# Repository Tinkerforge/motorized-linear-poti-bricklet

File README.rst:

Motorized Linear Poti Bricklet
==============================

This repository contains the firmware source code and the hardware design
files. The documentation generator configs can be found at
https://github.com/Tinkerforge/generators

Repository Content
------------------

software/:
 * examples/: Examples for all supported languages
 * build/: Compiled files
 * src/: Source code of firmware
 * Makefile: Makefile to build project

hardware/:
 * Contains KiCad project files and additionally schematics as PDF

datasheets/:
 * Contains datasheets for sensors and complex ICs that are used

Hardware
--------

The hardware is designed with the open source EDA Suite KiCad
(http://www.kicad.org). Before you are able to open the files,
you have to install the Tinkerforge kicad-libraries
(https://github.com/Tinkerforge/kicad-libraries). You can either clone
them directly in hardware/ or clone them in a separate folder and
symlink them into hardware/
(ln -s kicad_path/kicad-libraries project_path/hardware). After that you
can open the .pro file in hardware/ with KiCad and from there view and
modify the schematics and the PCB layout.

Software
--------

If you want to do your own Brick/Bricklet firmware development we highly
recommend that you use our build environment setup script and read the
tutorial (https://www.tinkerforge.com/en/doc/Tutorials/Tutorial_Build_Environment/Tutorial.html).

To compile the C code we recommend you to install the newest GNU Arm Embedded
Toolchain (https://launchpad.net/gcc-arm-embedded/+download).
You also need to install bricklib2 (https://github.com/Tinkerforge/bricklib2).

You can either clone it directly in software/src/ or clone it in a
separate folder and symlink it into software/src/
(ln -s bricklib_path/bricklib2 project_path/software/src/). Finally make sure to
have CMake installed (http://www.cmake.org/cmake/resources/software.html).

After that you can build the firmware by invoking make in software/.
The firmware (.zbin) can then be found in software/build/ and uploaded
with brickv (click button "Flashing" on start screen).

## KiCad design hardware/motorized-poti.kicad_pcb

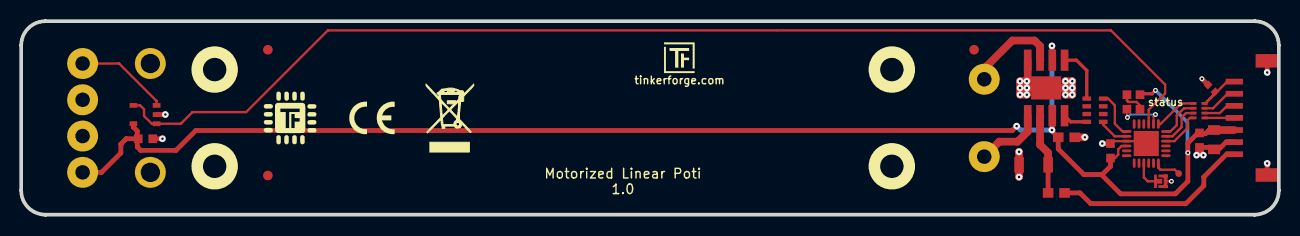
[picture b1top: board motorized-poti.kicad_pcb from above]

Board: 2 copper layers, 130.0 x 20.0 mm, 27 parts (0 on the bottom side), 24 nets.

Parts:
C1: 100nF; C0603E
C2: 10µF; C0805
C3: 47uF/10V; C1206
C4, C101: 100nF; C0603F
C5: 1µF; C0603F
C6: 220pF; C0402F
D1: blue; D0603F
Fiducial_Mark: VAL**; Fiducial_Mark
Fiducial_Mark#2, Fiducial_Mark#3: VAL**; Fiducial_Mark
J101: Debug; DEBUG_PAD
L1: FB; C0603E
P1: CON-SENSOR2
P2: MOTORIZED_POTI
P3: BOOT; SolderJumper
R1: 1k; R0603F
RP1: 1k; 4X0603
RP3: 82; 4X0402
U1: XMC1100-16; QFN24-4x4mm-0.5mm
U2: ZXBM5210; SO-8-EP
U3, U4, U5, U6: DRILL; DRILL_NP
U101: TLV271IDBVR; SOT23-5
VAL: CE_5mm

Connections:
+5V: L1.1, P1.1
AIN: U1.3, U101.1, U101.4
FWD: RP1.8, U1.8
GND: C1.2, C2.2, C3.1, C4.2, C5.2, C6.2, C101.2, P1.2, P1.EP, P2.3, P3.1, U1.9, U1.EXP, U2.8, U2.EP, U101.2
unnamed: C3.2, L1.2, U2.2
unnamed: C6.1, P1.7, RP3.4
unnamed: D1.2, R1.1
unnamed: J101.1, U1.18
unnamed: P1.4, RP3.1
unnamed: P1.5, RP3.2
unnamed: P1.6, RP3.3
unnamed: P2.4, U101.3
unnamed: P2.A, U2.7
unnamed: P2.B, U2.1
unnamed: P3.2, U1.15
unnamed: R1.2, U1.2
unnamed: RP1.1, U2.4
unnamed: RP1.4, U2.5
REV: RP1.5, U1.7
S-CLK: RP3.7, U1.23
S-CS: RP3.8, U1.22
S-MISO: RP3.5, U1.1
S-MOSI: RP3.6, U1.24
VCC: C1.1, C2.1, C4.1, C5.1, C101.1, D1.1, P1.3, P2.1, U1.10, U2.3, U2.6, U101.5

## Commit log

2015-11-17 add license stuff
2015-11-17 prototype of motorized linear poti bricklet
2015-12-22 adapt to alps poti
2016-02-09 Add WIP marker
2016-02-09 Add .gitignore
2017-03-03 partially placement, partial schematic
2017-03-03 restore proto placement
2017-03-07 Change to "new Bricklet" system with XMC1100
2017-03-16 Fix direction of LED D1
2017-03-16 Add connectors for power chaining
2017-03-16 Add new version of PCB layout
2017-03-22 Changed FWD/REV pins
2017-05-05 Change filtering to R/C circuit
2017-05-05 Move LED pin; add fiducial marks
2017-05-08 some footprints fixed, fix routing
2017-05-12 Fix logos
2017-05-18 connector distance to short hintt
2017-05-19 specify part values
2017-05-19 Fix SPI pins
2017-05-19 Fix orientation of J1
2017-05-19 Fix drill holes to grid
2017-05-19 Add 3d: motor driver
2017-05-29 fix mounting hole position, change wire angle
2017-05-31 modified prototype:
    * increase PCB length
    * change position of bricklet connector
    * add buffer for analog signal
    * remove external power input
    * fixed 5V supply over bricklet connector
2017-05-31 Add initial implementation of Motorized Linear Poti firmware
2017-06-01 Use uint16 as type for position
2017-06-01 Make sure we don't get overshoot by slowing down early enough
2017-06-01 Save/read calibration to/from flash
2017-06-01 Add new position function
2017-06-01 Add motor and calibration defines
2017-06-01 Remove debug
2017-08-11 specify filter circuit
2017-08-24 Newest hardware version uses inverting opamp, so we have to invert the poti position logic
2017-09-08 add status led description text
2017-09-19 specify processor
2017-11-02 Add 3d information (final)
2017-11-02 Add 3d model (*.step & *.FCStd)
2017-11-06 Add final schematic
2017-11-09 Fix colors
2017-11-16 change dnp l1 to fb
2017-11-16 Only return values between 0 and 100
2017-11-16 Increase speed of smooth motion a little bit
    (was getting stuck with some pots with the old value)
2017-11-16 Add 1% margin to min and max calibration value
    This way we can be sure that the end points are always reachable
    and we never physically touch the edges of the pot enclosure
2017-11-16 specify opamp more precise
2017-11-21 Rename file
2017-11-24 Add examples
2017-11-30 Update examples from generator
2017-12-07 mathematica: Also generate .nb files
2017-12-22 Make sure that poti value cant go back and forth between two values
2017-12-22 Add ref for 2.0.1
2018-01-26 c: Fine-tune printf format
2018-02-02 Update examples
2018-02-19 javascript: Close div tag correctly
2018-02-20 Cleanup KiCad libraries config
    Ensure LibDir=kicad-libraries and LibName1=tinkerforge.
    Remove special library.
2018-03-05 Remove unused flash-size define
2018-05-24 perl: Use strict in examples
2018-05-28 mathematica: Fix namespace
2018-06-06 Adapt to bricklib2 callback-value changes to fix wrong length of get-position packet
2018-06-06 Update changelog and version
2018-06-07 Add date ref for version 2.0.2 to changelog
2018-06-18 Change capacitor footprint(s) to C0402F
2018-06-18 Rename files
2018-06-28 Fix readme
2018-07-11 Add Makefile with docker support
2018-07-11 Update directory structure and build instructions
2018-07-11 Remove obsolete generate_makefile scripts
2018-10-04 Increase version for new release (changes in bricklib2)
2018-10-04 Add rev to changelog
2018-11-06 Add rust examples
2018-11-07 rust: Accept host names for ip connection, fix naming inconsistencies
2018-11-07 rust: Rename callback receivers.
2018-12-14 Add go examples.
2018-12-18 go: Change import path.
2018-12-18 go: Change import path again.
2018-12-20 rust: Reformat examples.
2019-01-24 mqtt: Add examples.
2019-01-24 mqtt: Fix example header.
2019-01-24 mqtt: Remove executable bit in example permissions.
2019-01-24 go: Minor example fixes.
2019-01-24 mqtt: Minor example fixes.
2019-03-28 mqtt: Fix whitespace.
2019-08-22 c: Adapt to bindings changes
2020-01-13 examples: Use python3 input instead of python2 raw_input.
2020-01-13 examples: mqtt: Remove trailing whitespace.
2020-03-16 Whitespace
2020-04-07 examples: rust: Always block when calling bindings functions.
2020-08-19 Add uc examples.
2020-08-25 uc: Fix whitespace
2020-08-27 uc: Fix warnings.
2020-08-31 uc: Use fixed-with placeholders in format strings.
2020-09-02 uc: Add example driver note.
2021-10-25 Update KiCad link
    https://www.kicad.org/blog/2021/10/Avoid-links-to-former-kicad-domain/
2022-04-19 examples: uc: Rename TF_HalContext to TF_HAL.
2022-04-27 uc: Adapt to bindings changes
2022-05-10 go: Fix format string
2022-07-06 Add license files.
2025-10-04 Fix compatibility with new Docker build image (GCC 14.2.1)

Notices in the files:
hardware/motorized-poti.kicad_pcb:
Licensed under CERN OHL v.1.1
Copyright (©) 2017, L.Lauer
Copyright Tinkerforge GmbH 2017.
This documentation describes Open Hardware and is licensed under the
CERN OHL v. 1.1.
